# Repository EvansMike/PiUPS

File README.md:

# PiUPS
An UPS hat for Raspberry Pi
See doc/UPS.adoc

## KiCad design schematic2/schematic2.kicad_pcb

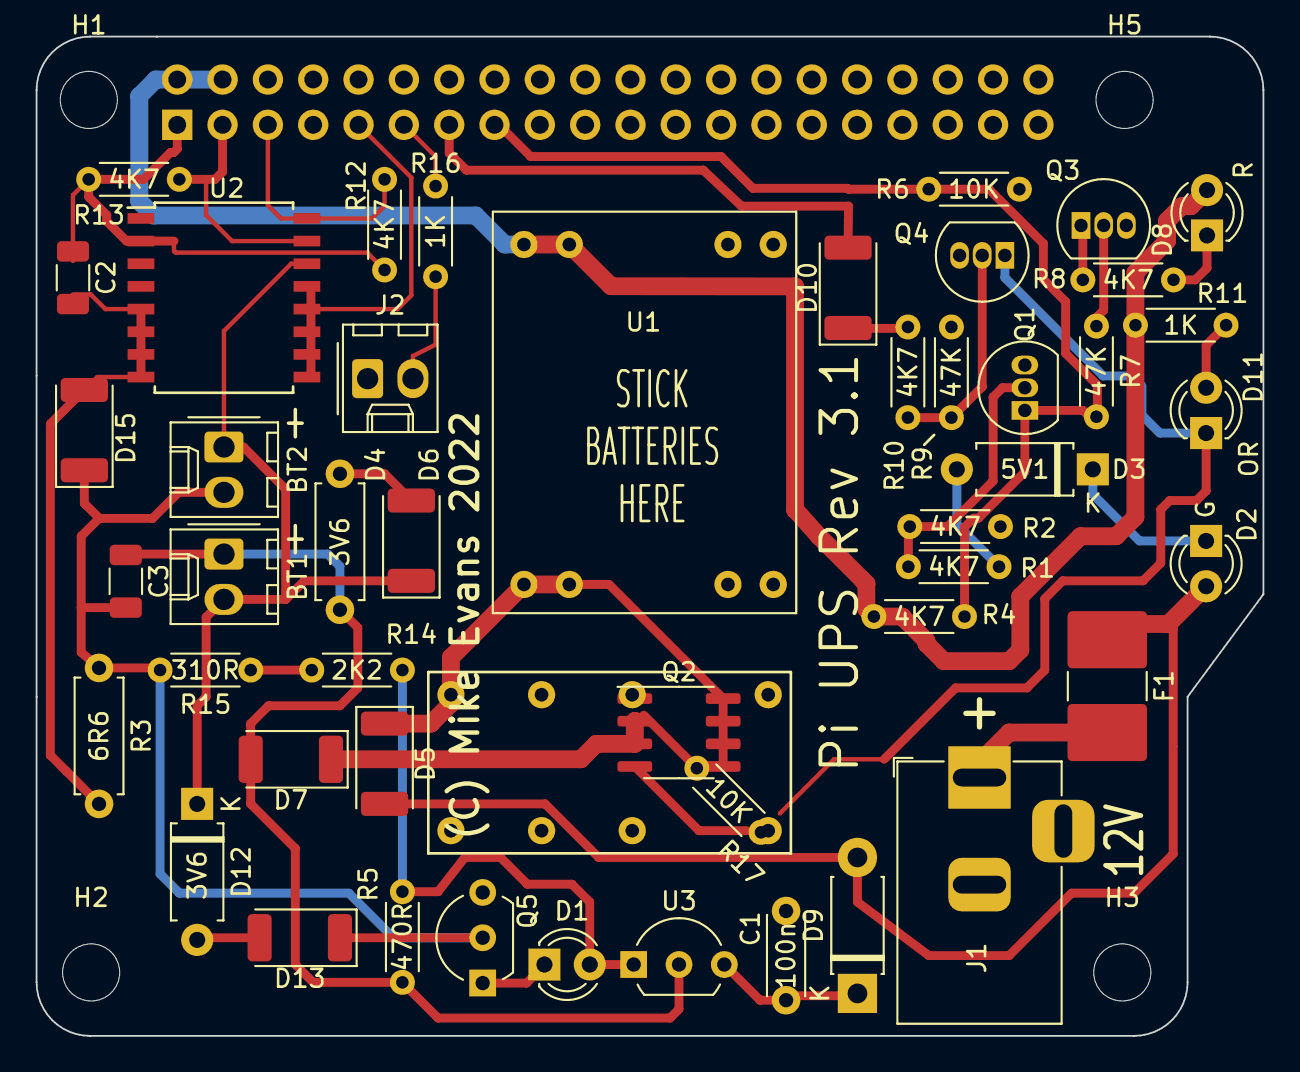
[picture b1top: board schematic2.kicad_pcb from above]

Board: 2 copper layers, 68.8 x 56.0 mm, 53 parts (1 on the bottom side), 32 nets.

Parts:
BT1, BT2: 302323 LiPo; Molex_KK-254_AE-6410-02A_1x02_P2.54mm_Vertical
C1: 100n; C_Disc_D4.3mm_W1.9mm_P5.00mm
C2: 100nF; C_1206_3216Metric
C3: 100n; C_1206_3216Metric
D1: LED; LED_D3.0mm
D2: G; LED_D3.0mm
D3: 5V1; D_A-405_P7.62mm_Horizontal
D4: 3V6; R_Axial_DIN0207_L6.3mm_D2.5mm_P7.62mm_Horizontal
D5, D6, D7, D13, D15: 1N4001; D_2010_5025Metric
D8: R; LED_D3.0mm
D9: 1N4148; D_DO-41_SOD81_P7.62mm_Horizontal
D10: 1N4148; D_2010_5025Metric
D11: OR; LED_D3.0mm
D12: 3V6; D_A-405_P7.62mm_Horizontal
F1: Polyfuse; Fuse_2816_7142Metric_Pad3.20x4.45mm_HandSolder
H1, H2, H3, H5: MountingHole; MountingHole_3.2mm_M3
J1: Barrel_Jack; BarrelJack_Horizontal
J2: Conn_01x02; Molex_KK-254_AE-6410-02A_1x02_P2.54mm_Vertical
K1: TIANBO_HJR_1-2C; Relay_DPDT_HJR_1-2C
P1: Conn_02x20_Odd_Even; PinSocket_2x20_P2.54mm_Vertical
Q1, Q3, Q4: BC547; TO-92_Inline
Q2: FDS9435A; SOIC-8_3.9x4.9mm_P1.27mm
Q5: BC547; TO-92L_Inline_Wide
R1, R2, R4, R8, R10, R12, R13: 4K7; R_Axial_DIN0204_L3.6mm_D1.6mm_P5.08mm_Horizontal
R3: 6R6; R_Axial_DIN0207_L6.3mm_D2.5mm_P7.62mm_Horizontal
R5: 470R; R_Axial_DIN0204_L3.6mm_D1.6mm_P5.08mm_Horizontal
R6, R17: 10K; R_Axial_DIN0204_L3.6mm_D1.6mm_P5.08mm_Horizontal
R7, R9: 47K; R_Axial_DIN0204_L3.6mm_D1.6mm_P5.08mm_Horizontal
R11, R16: 1K; R_Axial_DIN0204_L3.6mm_D1.6mm_P5.08mm_Horizontal
R14: 2K2; R_Axial_DIN0204_L3.6mm_D1.6mm_P5.08mm_Horizontal
R15: 310R; R_Axial_DIN0204_L3.6mm_D1.6mm_P5.08mm_Horizontal
U1: buck; BUCK_MODULE_5V
U2: DS3231M; SOIC-16W_7.5x10.3mm_P1.27mm
U3: LM317_SOT-223; TO-92L_Inline_Wide

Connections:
+3V3: C2.1, P1.1, R12.2, R13.2, U2.2
+5V: D8.2, P1.2, P1.4, R4.2, R11.2, U1.4
+12V: D2.2, D5.2, D9.2, F1.1
CLK_BAT: BT1.2, BT2.1, D6.1, D12.1, U2.14
GND: C1.2, C2.2, D15.2, J1.2, J2.1, P1.6, P1.9, P1.14, P1.20, P1.25, P1.30, P1.34, P1.39, Q1.3, Q3.3, Q4.3, Q5.3, R2.2, R3.2, R6.1, R9.1, U1.2, U1.3, U2.5, U2.6, U2.7, U2.8, U2.9, U2.10, U2.11, U2.12, U2.13
GPIO17: P1.11, R16.1
unnamed: BT1.1, C3.1, D4.1, D7.2, R5.1, U3.2
unnamed: BT2.2, C3.2, D13.1, D15.1, Q5.2, R3.1, R15.2
unnamed: C1.1, D9.1, U3.3
unnamed: D1.1, Q5.1
unnamed: D1.2, R5.2, R14.1, U3.1
unnamed: D2.1, D3.1
unnamed: D3.2, R1.1
unnamed: D4.2, D6.2
unnamed: D5.1, Q2.5, Q2.6, Q2.7, Q2.8, U1.1
unnamed: D7.1, Q2.1, Q2.2, Q2.3, R17.1
unnamed: D8.1, R8.2
unnamed: D10.1, R10.1
unnamed: D11.1, Q2.4, Q4.1, R17.2
unnamed: D11.2, R11.1
unnamed: D12.2, D13.2
unnamed: F1.2, J1.1
unnamed: J2.2, R16.2
unnamed: Q1.2, R1.2, R2.1
unnamed: Q3.1, R8.1
unnamed: Q3.2, R7.1
unnamed: Q4.2, R9.2, R10.2
unnamed: R14.2, R15.1
PI_P_SIG: D10.2, P1.13
POWER_FAIL: P1.15, Q1.1, R4.1, R6.2, R7.2
SCL1: P1.5, R12.1, U2.16
SDA1: P1.3, R13.1, U2.15

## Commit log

2018-07-06 new file: schematic2.kicad_pcb new file: schematic2.lib new file: schematic2.sch
2018-07-10 modified: schematic2/schematic2.kicad_pcb new file: schematic2/schematic2.pro modified: schematic2/schematic2.sch
2018-07-12 add fuse and logo.
2018-07-12 Add cache. new file: schematic2-cache.lib
2018-07-12 Change clock for discreets.
2018-07-12 Convert blocks to sheets.
    At this point only the schematic is changed.
2018-07-12 Layout done.
2018-07-13 Put the prebuilt buck converter back.
    It's cheaper and easier.
2018-07-24 Final V1 Ordered.
2018-07-26 Added EEPROM
2018-07-26 Fix wrongly connected clock battery reg
2018-08-09 Runs on the Pi to call shutddown if the power outage is long enough, new file: powermon.py
2018-08-09 Fix it so it works.
2018-08-09 Fix wron wiring to clock.
2018-08-09 Bug#196
    Working. Could be better. Perhaps 2 callbacks, rising & falling.
2018-08-09 Added sub sheet and some annotations. new file: powermon.service
2018-08-09 Added content to empty file. modified: powermon.service
2018-08-15 Power the 3V line instead of the 5V.
2018-12-09 Re-layout.
2018-12-22 Stuff;
2018-12-24 Remove timestamps in log messages.
    Messages are stamped by the system.
2018-12-24 new file: UPS.adoc
2019-01-24 modified: doc/UPS.adoc modified: firmware/src/powermon.py modified: schematic2/schematic2-cache.lib modified: schematic2/schematic2.kicad_pcb modified: schematic2/schematic2.sch
2021-08-05 Mostly layout changes.
2021-08-05 Sch. Moved stuff for aesthetics.
2021-08-11 modified: schematic2.kicad_pcb
2021-08-11 Remove un-needed FET.
2022-03-18 Boards ordered.
2022-03-21 Revert back to KiCAD5
    Because the benchy pi cannont run V6.
2022-03-21 Update powermon.py a bit.
    Also move stuff.
2022-04-03 Update docs.
2022-04-03 new file: release_note-101.adoc
2022-04-03 Detail changes made from release note.
2022-04-03 modified: UPS.adoc
2022-04-04 modified: doc/UPS.adoc
2022-04-04 More.
2022-04-13 Better view of amended assembly.
2022-05-26 Update build instructions.
2022-05-26 Add sch pdf.
